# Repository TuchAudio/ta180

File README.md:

# ta180
Ceramic Phono Cartridge buffer

## Purpose
It provides a **high-impedance** input (1 Mohm) suitable for _ceramic phono cartridges_ in order to connect them to a regular _line_ input (typically 47 kohm).

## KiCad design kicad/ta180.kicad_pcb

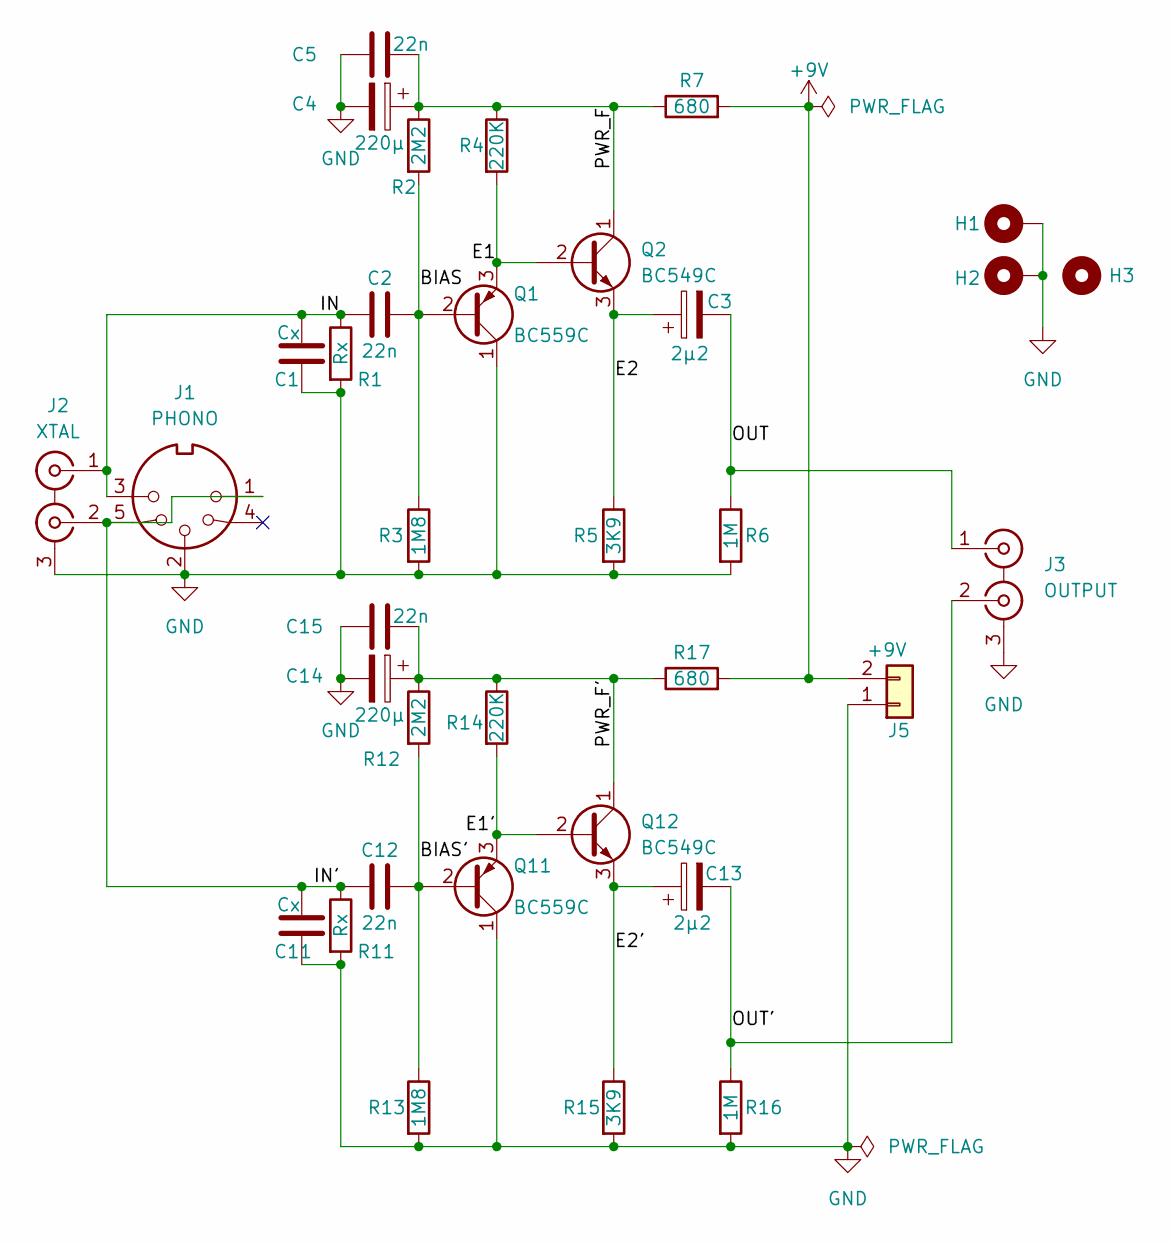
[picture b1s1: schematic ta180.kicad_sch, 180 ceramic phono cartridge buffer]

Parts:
C1, C11: Cx; PinSocket_1x02_P2.54mm_Vertical
C2, C12: 22n; C_Rect_L7.2mm_W2.5mm_P5.00mm_FKS2_FKP2_MKS2_MKP2
C3, C13: 2µ2; CP_Radial_D4.0mm_P1.50mm
C4, C14: 220µ; CP_Radial_D6.3mm_P2.50mm
C5, C15: 22n; C_Disc_D6.0mm_W2.5mm_P5.00mm
H1, H2: MountingHole_Pad; MountingHole_3.2mm_M3_DIN965_Pad
H3: MountingHole; MountingHole_3.2mm_M3
J1: PHONO; DIN 5-180deg
J2: XTAL; 2xRCA_vertical
J3: OUTPUT; 2xRCA_vertical
J5: +9V; JST_EH_S2B-EH_1x02_P2.50mm_Horizontal
Q1, Q11: BC559C; TO-92_Inline
Q2, Q12: BC549C; TO-92_Inline
R1, R11: Rx; PinSocket_1x02_P2.54mm_Vertical
R2, R12: 2M2; R_Axial_DIN0207_L6.3mm_D2.5mm_P10.16mm_Horizontal
R3, R13: 1M8; R_Axial_DIN0207_L6.3mm_D2.5mm_P10.16mm_Horizontal
R4, R14: 220K; R_Axial_DIN0207_L6.3mm_D2.5mm_P10.16mm_Horizontal
R5, R15: 3K9; R_Axial_DIN0207_L6.3mm_D2.5mm_P10.16mm_Horizontal
R6, R16: 1M; R_Axial_DIN0207_L6.3mm_D2.5mm_P10.16mm_Horizontal
R7, R17: 680; R_Axial_DIN0207_L6.3mm_D2.5mm_P10.16mm_Horizontal

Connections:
+9V: J5.2, R7.2, R17.2
/BIAS: C2.2, Q1.2 (B), R2.2, R3.1
/BIAS': C12.2, Q11.2 (B), R12.2, R13.1
/E1: Q1.3 (E), Q2.2 (B), R4.2
/E1': Q11.3 (E), Q12.2 (B), R14.2
/E2: C3.1, Q2.3 (E), R5.1
/E2': C13.1, Q12.3 (E), R15.1
/IN: C1.1, C2.1, J1.3, J2.1 (IN1), R1.1
/IN': C11.1, C12.1, J1.1, J1.5, J2.2 (IN2), R11.1
/OUT: C3.2, J3.1 (IN1), R6.1
/OUT': C13.2, J3.2 (IN2), R16.1
/PWR_F: C4.1, C5.2, Q2.1 (C), R2.1, R4.1, R7.1
/PWR_F': C14.1, C15.2, Q12.1 (C), R12.1, R14.1, R17.1
GND: C1.2, C4.2, C5.1, C11.2, C14.2, C15.1, H1.1, H2.1, J1.2, J2.3 (EXT), J3.3 (EXT), J5.1, Q1.1 (C), Q11.1 (C), R1.2, R3.2, R5.2, R6.2, R11.2, R13.2, R15.2, R16.2

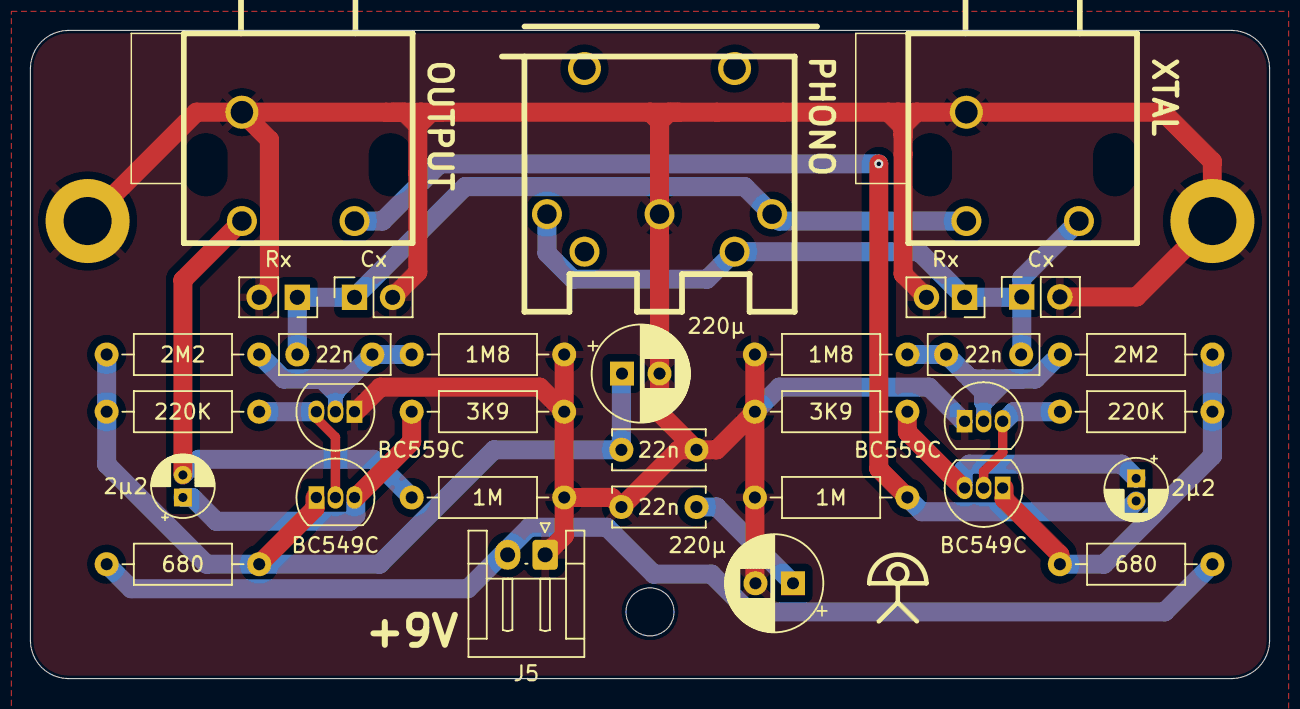
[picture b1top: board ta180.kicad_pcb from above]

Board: 2 copper layers, 82.5 x 43.2 mm, 35 parts (0 on the bottom side), 14 nets.

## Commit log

2025-11-08 add KiCAD files
2025-11-12 Add purpose section to README
    Added purpose section explaining high-impedance input for ceramic phono cartridges.
